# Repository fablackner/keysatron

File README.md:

# Keysatron

**Keysatron** is an inline USB-to-USB hardware adapter designed to intercept, transform, and remap USB HID keyboard input in real-time. By sitting transparently between your physical keyboard and your computer, it allows hardware-level key translation—such as converting German ISO (QWERTZ) keystrokes into Colemak ISO layout—without requiring any software, drivers, or administrative privileges on the host operating system.

---

## Hardware Overview

Keysatron is built around the **STM32F405RGT6** ARM Cortex-M4 microcontroller, which features two independent USB OTG controllers:
1. **USB OTG FS (Full-Speed)**: Operates as **USB Host** on port `USB_IN` (J2) to read input reports from connected USB keyboards.
2. **USB OTG HS (with embedded Full-Speed PHY)**: Operates as **USB Device** on port `USB_PC` (J3) to emulate a USB HID keyboard to the host PC.

### Specifications

| Feature | Description |
| :--- | :--- |
| **Microcontroller** | STM32F405RGT6 (ARM Cortex-M4 @ 168 MHz, 1 MB Flash, 192 KB SRAM) |
| **Input Port (`USB_IN`, J2)** | USB Type-A Female – USB OTG FS Host (PA11 `DM`, PA12 `DP`) |
| **Output Port (`USB_PC`, J3)** | USB Type-A Female / Cable – USB OTG HS Device in FS mode (PB14 `DM`, PB15 `DP`) |
| **Power Supply** | MP2451DT step-down buck converter (5 V VBUS to 3.3 V core rail) |
| **Oscillator** | 16 MHz external crystal (HSE) |
| **ESD Protection** | SRV05-4 transient voltage suppressors on USB data lines |
| **Status LEDs** | Red LED (`D1`): Power indicator (3.3 V rail)<br>Green LED (`D3`): Status / activity indicator (GPIO `PA0`) |
| **Debug Header** | 5-pin 2.54 mm SWD header (`J1`) |

---

## SWD Header Pinout (`J1`)

The board provides a 5-pin single-row header (`J1`, 2.54 mm pitch) for programming and debugging via SWD:

```
[ 1: GND ] [ 2: NRST ] [ 3: CLK ] [ 4: IO ] [ 5: 3.3V ]
```

| Pin | Label | STM32 Pin | Function |
| :---: | :---: | :---: | :--- |
| **1** | `GND` | `VSS` (Pins 12, 18, 60, 63) | Ground |
| **2** | `NRST` | `NRST` (Pin 7) | Active-low system reset |
| **3** | `CLK` | `PA14` (Pin 49) | SWD Clock (`SWCLK`) |
| **4** | `IO` | `PA13` (Pin 46) | SWD Data (`SWDIO`) |
| **5** | `3.3V` | `VDD` (Pins 1, 13, 19, 32, 48, 64) | 3.3 V Power rail |

### Connecting to an ST-LINK / Nucleo Debugger

When using the built-in ST-LINK/V2-1 on an STM32 Nucleo-64 board (CN4 header):

> [!IMPORTANT]
> **Remove the two jumpers on `CN2`** on the Nucleo board to disconnect the debugger from the onboard microcontroller and direct SWD lines to header `CN4`.
> 
> Note that `CN4` Pin 1 (`VDD_TARGET`) is a voltage-sensing line and does **not** power the target. Power Keysatron via USB or connect `3V3` from the Nucleo power header (`CN6` Pin 4) to Keysatron `J1` Pin 5.

Wiring between Nucleo `CN4` and Keysatron `J1`:

| Nucleo CN4 Pin | Nucleo Function | Wire to Keysatron `J1` Pin | Keysatron Function |
| :---: | :---: | :---: | :---: |
| Pin 1 | `VDD_TARGET` | **Pin 5** | `3.3V` |
| Pin 2 | `SWCLK` | **Pin 3** | `CLK` |
| Pin 3 | `GND` | **Pin 1** | `GND` |
| Pin 4 | `SWDIO` | **Pin 4** | `IO` |
| Pin 5 | `NRST` | **Pin 2** | `NRST` |

---

## Repository Contents

- `keysatron.kicad_pcb` – KiCad PCB layout (4-layer board)
- `keysatron.sch` – KiCad schematic
- `keysatron.pro` – KiCad project configuration
- `keysatron.csv` – Bill of Materials (BOM) with LCSC component part numbers
- `assembly/` – Pick-and-place component position files (`keysatron-all-pos.csv`) and BOM (`keysatron_bom.csv`) for automated assembly
- `gerber/` – Gerber fabrication files and drill files ready for PCB manufacturing (`keysatron_gerber.zip`)

---

## Firmware

The companion firmware for this board is maintained in the [keysatron-firmware](https://github.com/fablackner/keysatron-firmware) repository.

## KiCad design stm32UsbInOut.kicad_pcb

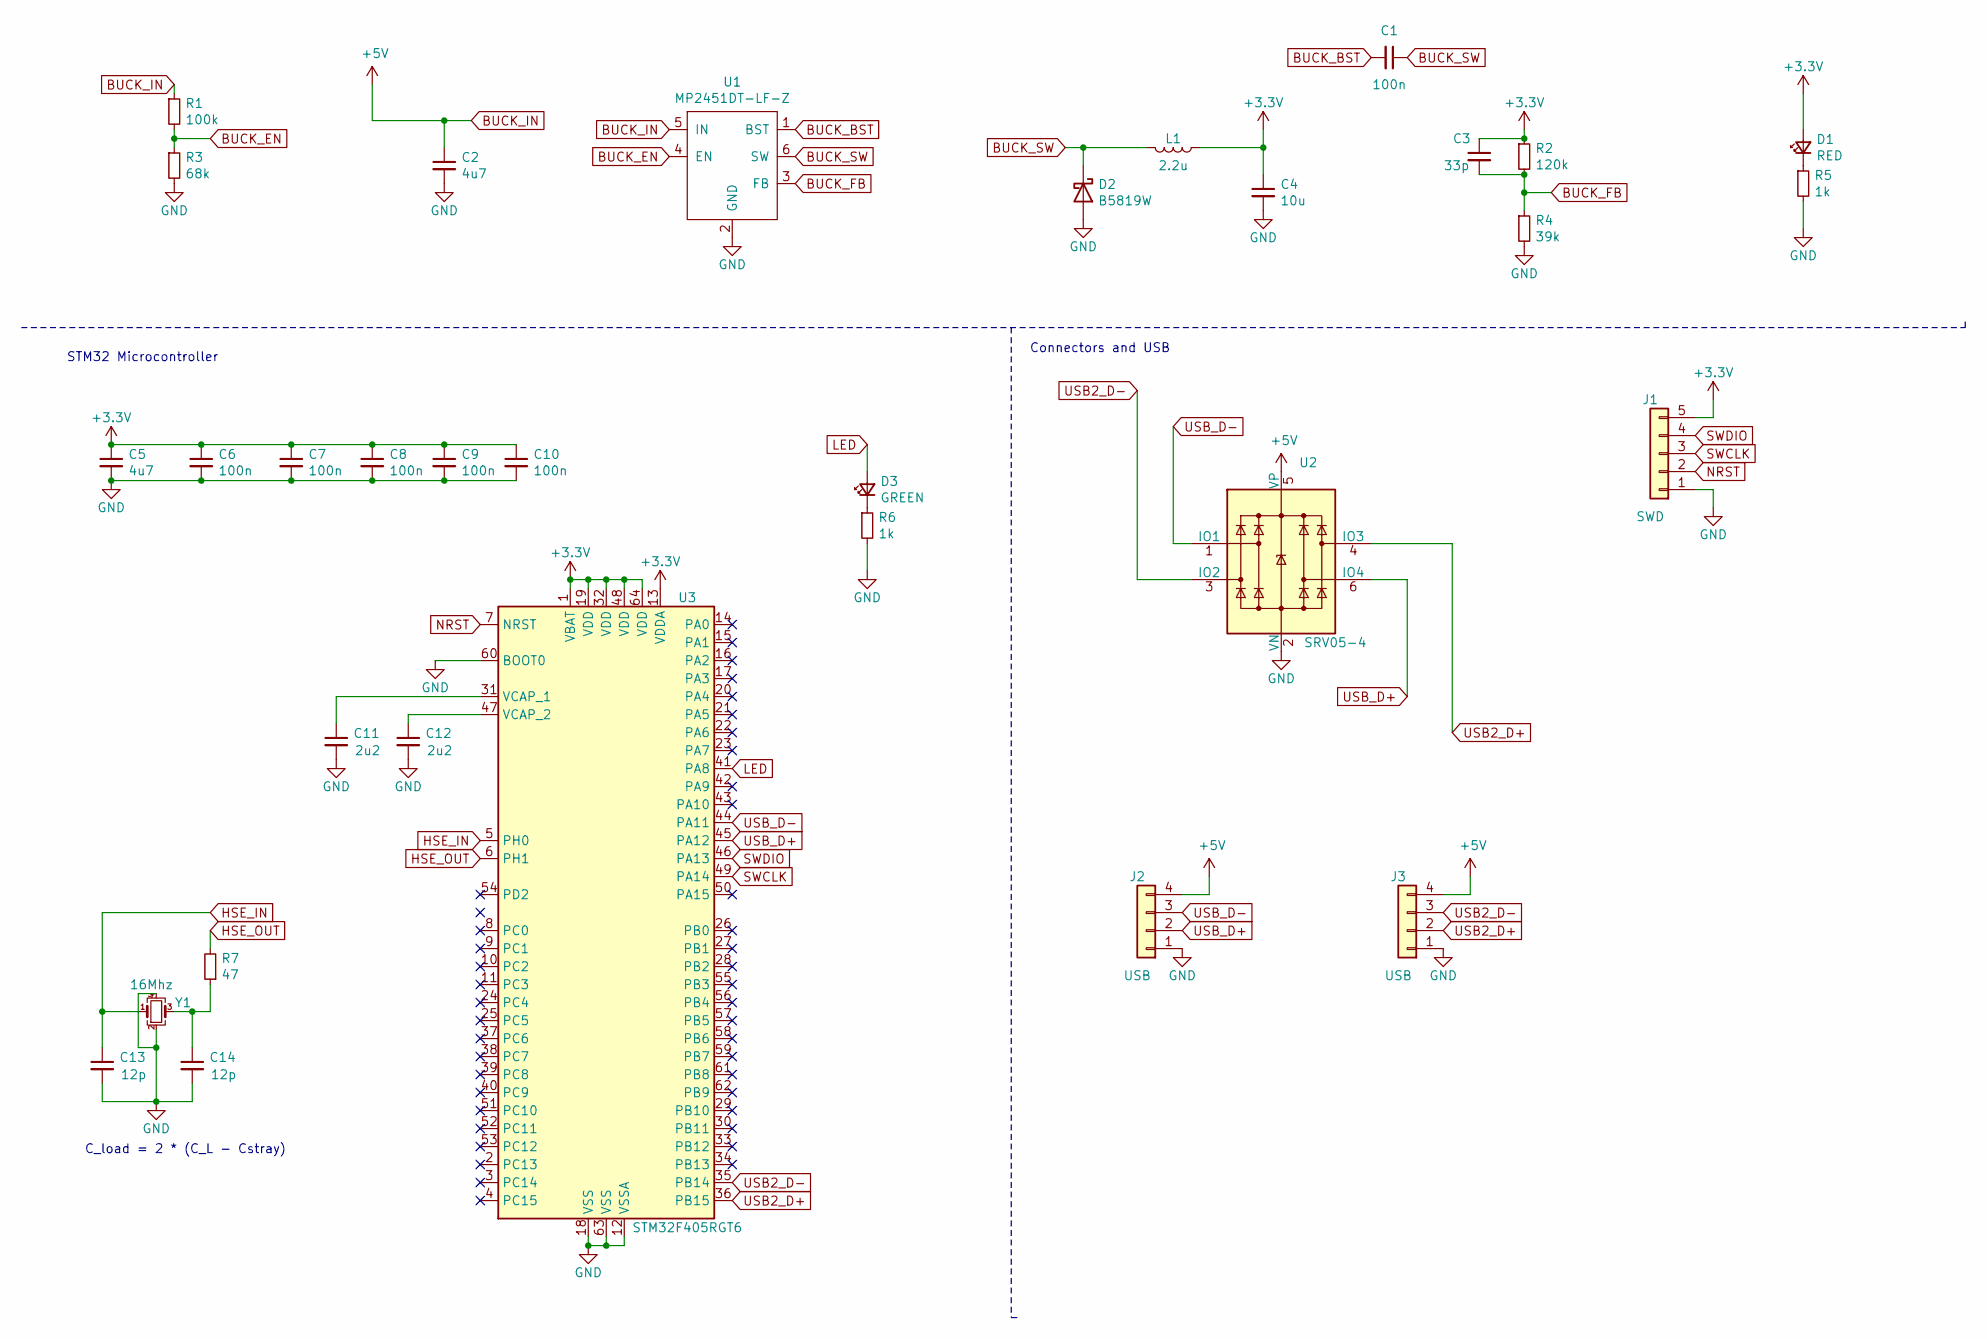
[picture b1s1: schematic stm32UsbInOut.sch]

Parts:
C1: 100n; C_0603_1608Metric
C2: 4u7; C_1206_3216Metric
C3: 33p; C_0603_1608Metric
C4: 10u; C_1206_3216Metric
C5: 4u7; C_0603_1608Metric
C6, C7, C8, C9, C10: 100n; C_0402_1005Metric
C11, C12: 2u2; C_0603_1608Metric
C13, C14: 12p; C_0402_1005Metric
D1: RED; D_0603_1608Metric
D2: B5819W; D_SOD-123
D3: GREEN; D_0603_1608Metric
J1: SWD; PinHeader_1x05_P2.54mm_Vertical
J2, J3: USB; USB_A_Molex_67643_Horizontal
L1: 2.2u; L_Sunlord_MWSA0518_5.4x5.2mm
R1: 100k; R_0603_1608Metric
R2: 120k; R_0603_1608Metric
R3: 68k; R_0603_1608Metric
R4: 39k; R_0603_1608Metric
R5, R6: 1k; R_0603_1608Metric
R7: 47; R_0402_1005Metric
U1: MP2451DT-LF-Z; SOT-23-6
U2: SRV05-4; SOT-23-6
U3: STM32F405RGT6; LQFP-64_10x10mm_P0.5mm
Y1: 16Mhz; Crystal_SMD_3225-4Pin_3.2x2.5mm

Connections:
+3V3: C3.1, C4.1, C5.1, C6.1, C7.1, C8.1, C9.1, C10.1, D1.2 (A), J1.5, L1.1, R2.1, U3.1 (VBAT), U3.13 (VDDA), U3.19 (VDD), U3.32 (VDD), U3.48 (VDD), U3.64 (VDD)
BUCK_BST: C1.2, U1.1 (BST)
BUCK_EN: R1.2, R3.1, U1.4 (EN)
BUCK_FB: C3.2, R2.2, R4.1, U1.3 (FB)
BUCK_IN: C2.1, J2.4, J3.4, R1.1, U1.5 (IN), U2.5 (VP)
BUCK_SW: C1.1, D2.1 (K), L1.2, U1.6 (SW)
GND: C2.2, C4.2, C5.2, C6.2, C7.2, C8.2, C9.2, C10.2, C11.2, C12.2, C13.2, C14.2, D2.2 (A), J1.1, J2.1, J3.1, R3.2, R4.2, R5.2, R6.2, U1.2 (GND), U2.2 (VN), U3.12 (VSSA), U3.18 (VSS), U3.60 (BOOT0), U3.63 (VSS), Y1.2, Y1.4
HSE_IN: C13.1, U3.5 (PH0), Y1.1
HSE_OUT: R7.2, U3.6 (PH1)
LED: D3.2 (A), U3.41 (PA8)
NRST: J1.2, U3.7 (NRST)
unnamed: C11.1, U3.31 (VCAP_1)
unnamed: C12.1, U3.47 (VCAP_2)
unnamed: C14.1, R7.1, Y1.3
unnamed: D1.1 (K), R5.1
unnamed: D3.1 (K), R6.1
SWCLK: J1.3, U3.49 (PA14)
SWDIO: J1.4, U3.46 (PA13)
USB2_D+: J3.2, U2.4 (IO3), U3.36 (PB15)
USB2_D-: J3.3, U2.3 (IO2), U3.35 (PB14)
USB_D+: J2.2, U2.6 (IO4), U3.45 (PA12)
USB_D-: J2.3, U2.1 (IO1), U3.44 (PA11)

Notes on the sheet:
C_load = 2 * (C_L - Cstray)
STM32 Microcontroller
Connectors and USB

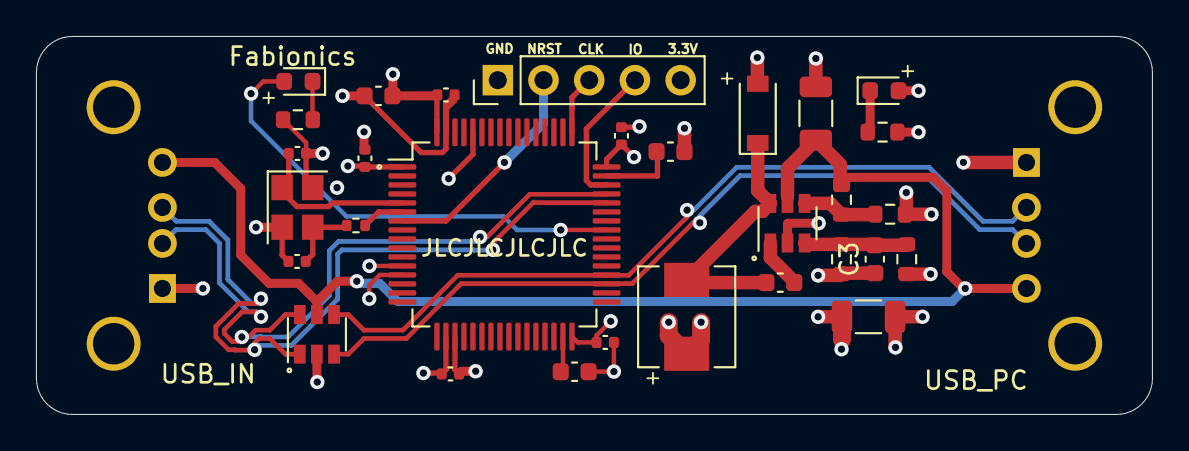
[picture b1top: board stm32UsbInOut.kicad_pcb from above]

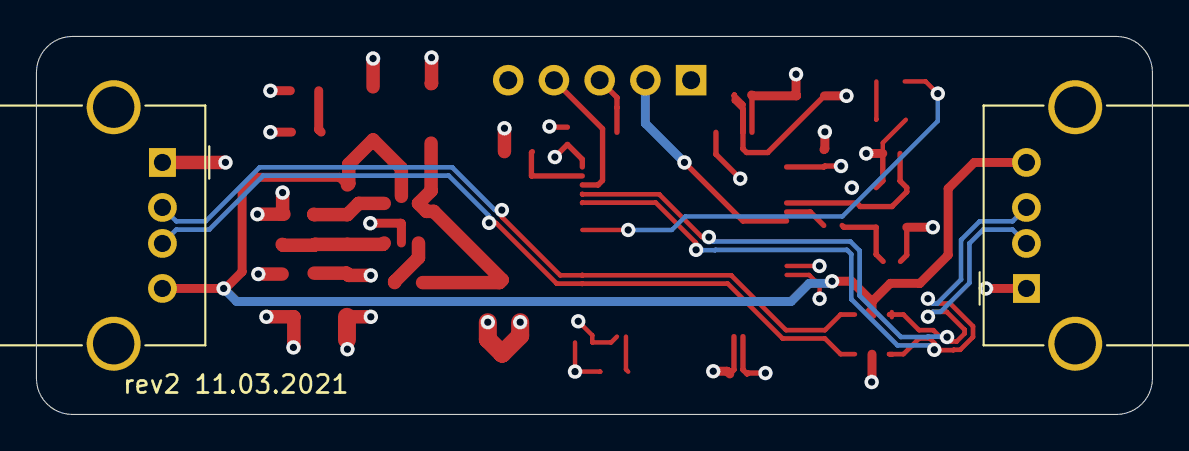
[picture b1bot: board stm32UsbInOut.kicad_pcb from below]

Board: 4 copper layers, 62.0 x 21.0 mm, 32 parts (2 on the bottom side), 22 nets.
